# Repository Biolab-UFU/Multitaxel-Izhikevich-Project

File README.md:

# Sensor Multitaxel com Modelo de Izhikevich

## 📌 **Descrição do Projeto**
Este projeto consiste na aplicação do **Modelo de Izhikevich** para a detecção de **escorregamento** em uma **matriz piezoresistiva**, acoplada à ponta dos dedos de uma **prótese robótica**. A matriz é composta por **4 linhas e 4 colunas**, formando um total de **16 unidades tácteis (taxels)**.

A leitura do sensor é realizada por uma **placa Nucleo STM32F767ZI**, com o firmware desenvolvido na **STM32CubeIDE**. O processamento do sinal permite detectar padrões tácteis e inferir a presença de escorregamento, contribuindo para o aprimoramento do controle da prótese.

---

## 🛠 **Arquitetura do Sistema**
### 🔹 **Hardware**
- **Matriz piezoresistiva:** 4×4 taxels.
- **Placa de aquisição:** Utiliza **multiplexadores** para selecionar os taxels.
- **Filtro passa-baixa de 10Hz:** Realiza o pré-processamento dos sinais.
- **STM32F767ZI:** Responsável pela aquisição e processamento do sinal.

### 🔹 **Esquema de Leitura**
- **As 4 colunas** da matriz estão conectadas aos **canais do ADC1** do STM32F767, com **pull-up de 5.6kΩ**.
- **As 4 linhas** estão conectadas a **GPIOs** e são ativadas sequencialmente para permitir a multiplexação.
- O firmware controla a ativação das linhas e a aquisição dos valores analógicos das colunas via **ADC**, permitindo a reconstrução da distribuição de pressão na matriz.

---

## 🧠 **Modelo de Izhikevich**
O modelo de **Izhikevich (2003)** é um modelo matemático de neurônios que equilibra **simplicidade computacional** e **realismo biológico**. Ele é definido pelas seguintes equações diferenciais:

$$
\frac{dv}{dt} = 0.04v^2 + 5v + 140 - u + I
$$

$$
\frac{du}{dt} = a(bv - u)
$$

Se v ≥ 30mV, então: v ← c, u ← u + d

Onde:
- **v** representa o potencial de membrana do neurônio.
- **u** é uma variável de recuperação do neurônio.
- **I** é a corrente de entrada.
- **a, b, c, d** são parâmetros ajustáveis que definem diferentes tipos de comportamento neural.

Quando **v atinge 30mV**, ocorre um disparo neuronal, e ele é resetado.

No contexto deste projeto, esse modelo é aplicado à saída da matriz tátil, permitindo a identificação de padrões temporais associados ao **escorregamento**.

---

## 📂 **Estrutura do Repositório**
📁 /STM32F767 - A documentação necessária para o desenvolvimento na Nucleo Board (Ler Main User Manual e Reference Manual).  

📁 /hardware - Hardware, Esquemáticos e diagramas do sensor multitaxel.  

📁 /firmware - Código-fonte para aquisição, geração e processamento dos sinais, e visualização gráfica.  

📁 /Artigos - Artigos desenvolvidos pelo Biolab, e pelo laboratório SINAPSE de Singapura (fabricante do sensor), além de artigos úteis.  

Cada subdiretório contém um **README** específico com detalhes sobre sua funcionalidade.

---

## 🚀 **Como Usar**
### 📌 **Requisitos**
- **Placa STM32F767ZI**
- **STM32CubeIDE**
- **Cabo USB para programação**

### 🔧 **Passos**
1. Clone este repositório:  
   ```bash
   git clone https://github.com/stephan-biomedical-engineer/Biolab.git
   ```
2. Abra o **STM32CubeIDE** e importe o projeto.
3. Compile e grave o firmware na placa.
4. Conecte o sensor e monitore a aquisição dos sinais.

---

## 📜 **Referências**
- Izhikevich, E. M. (2003). "Simple Model of Spiking Neurons". _IEEE Transactions on Neural Networks._
- Documentação da **STMicroelectronics** para o STM32F767ZI.

---

📌 **Autor:** Stephan Costa Barros  
📅 **Última atualização:** 29/03/2025
💡 **Contato:** stephanbrrs8@gmail.com

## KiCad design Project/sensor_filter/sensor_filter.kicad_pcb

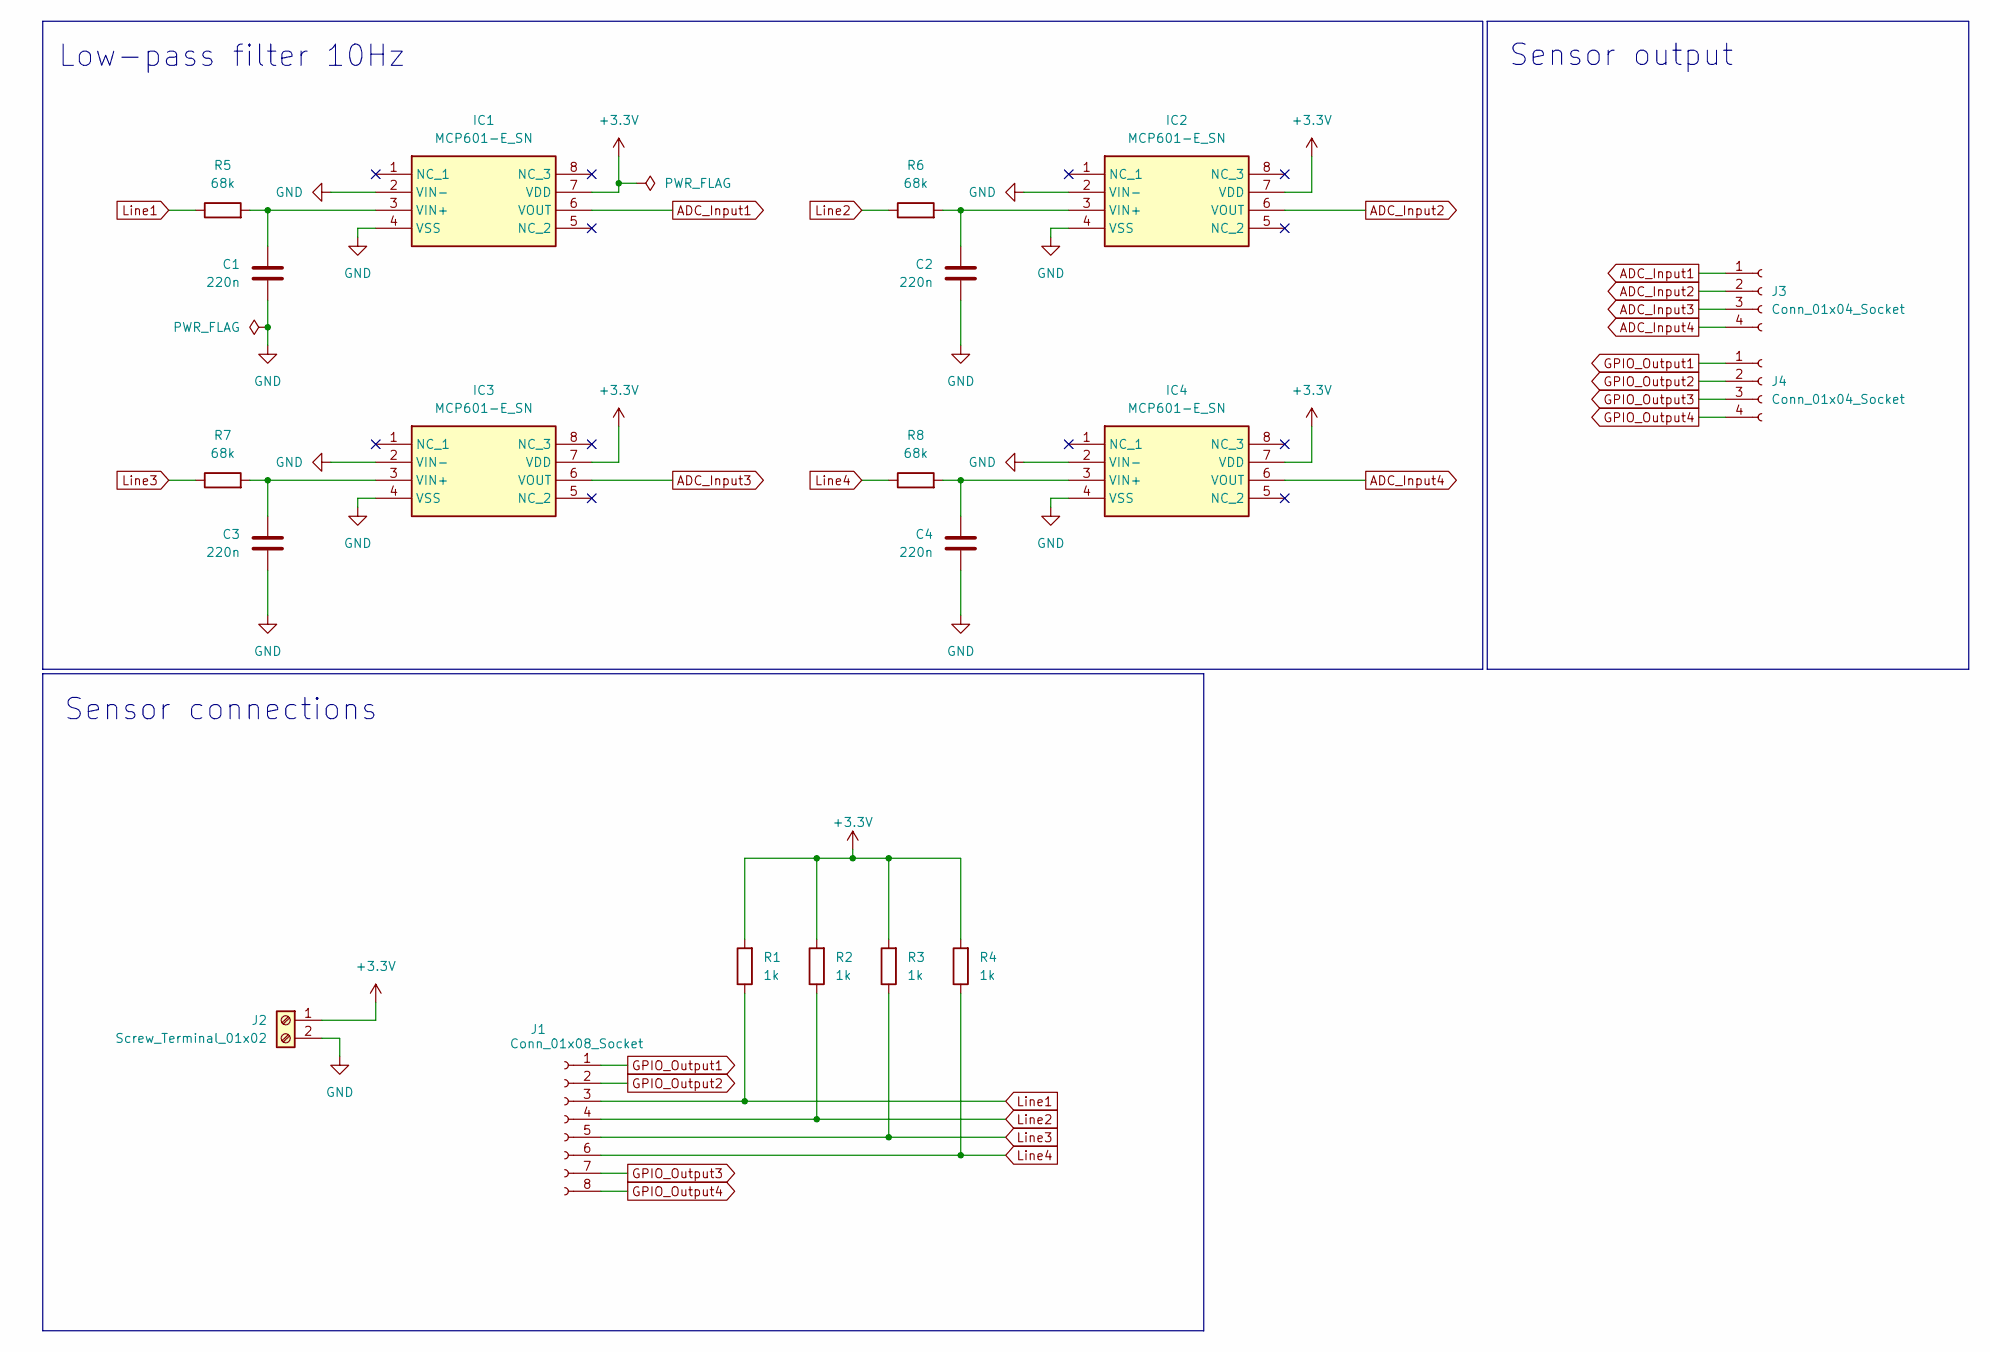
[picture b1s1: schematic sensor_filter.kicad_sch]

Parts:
C1, C2, C3, C4: 220n; CP_Radial_Tantal_D4.5mm_P2.50mm
IC1, IC2, IC3, IC4: MCP601-E_SN; SOIC127P600X175-8N; Mouser Part Number 579-MCP601-E/SN
J1: Conn_01x08_Socket; PinSocket_1x08_P2.54mm_Vertical
J2: Screw_Terminal_01x02; TerminalBlock_MaiXu_MX126-5.0-02P_1x02_P5.00mm
J3, J4: Conn_01x04_Socket; PinSocket_1x04_P2.54mm_Vertical
R1, R2, R3, R4: 1k; R_Axial_DIN0207_L6.3mm_D2.5mm_P7.62mm_Horizontal
R5, R6, R7, R8: 68k; R_Axial_DIN0207_L6.3mm_D2.5mm_P7.62mm_Horizontal

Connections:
+3.3V: IC1.7 (VDD), IC2.7 (VDD), IC3.7 (VDD), IC4.7 (VDD), J2.1, R1.2, R2.2, R3.2, R4.2
ADC_Input1: IC1.6 (VOUT), J3.1
ADC_Input2: IC2.6 (VOUT), J3.2
ADC_Input3: IC3.6 (VOUT), J3.3
ADC_Input4: IC4.6 (VOUT), J3.4
GND: C1.2, C2.2, C3.2, C4.2, IC1.2 (VIN-), IC1.4 (VSS), IC2.2 (VIN-), IC2.4 (VSS), IC3.2 (VIN-), IC3.4 (VSS), IC4.2 (VIN-), IC4.4 (VSS), J2.2
GPIO_Output1: J1.1, J4.1
GPIO_Output2: J1.2, J4.2
GPIO_Output3: J1.7, J4.3
GPIO_Output4: J1.8, J4.4
Line1: J1.3, R1.1, R5.1
Line2: J1.4, R2.1, R6.1
Line3: J1.5, R3.1, R7.1
Line4: J1.6, R4.1, R8.1
unnamed: C1.1, IC1.3 (VIN+), R5.2
unnamed: C2.1, IC2.3 (VIN+), R6.2
unnamed: C3.1, IC3.3 (VIN+), R7.2
unnamed: C4.1, IC4.3 (VIN+), R8.2

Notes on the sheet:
Sensor connections
Low-pass filter 10Hz
Sensor output

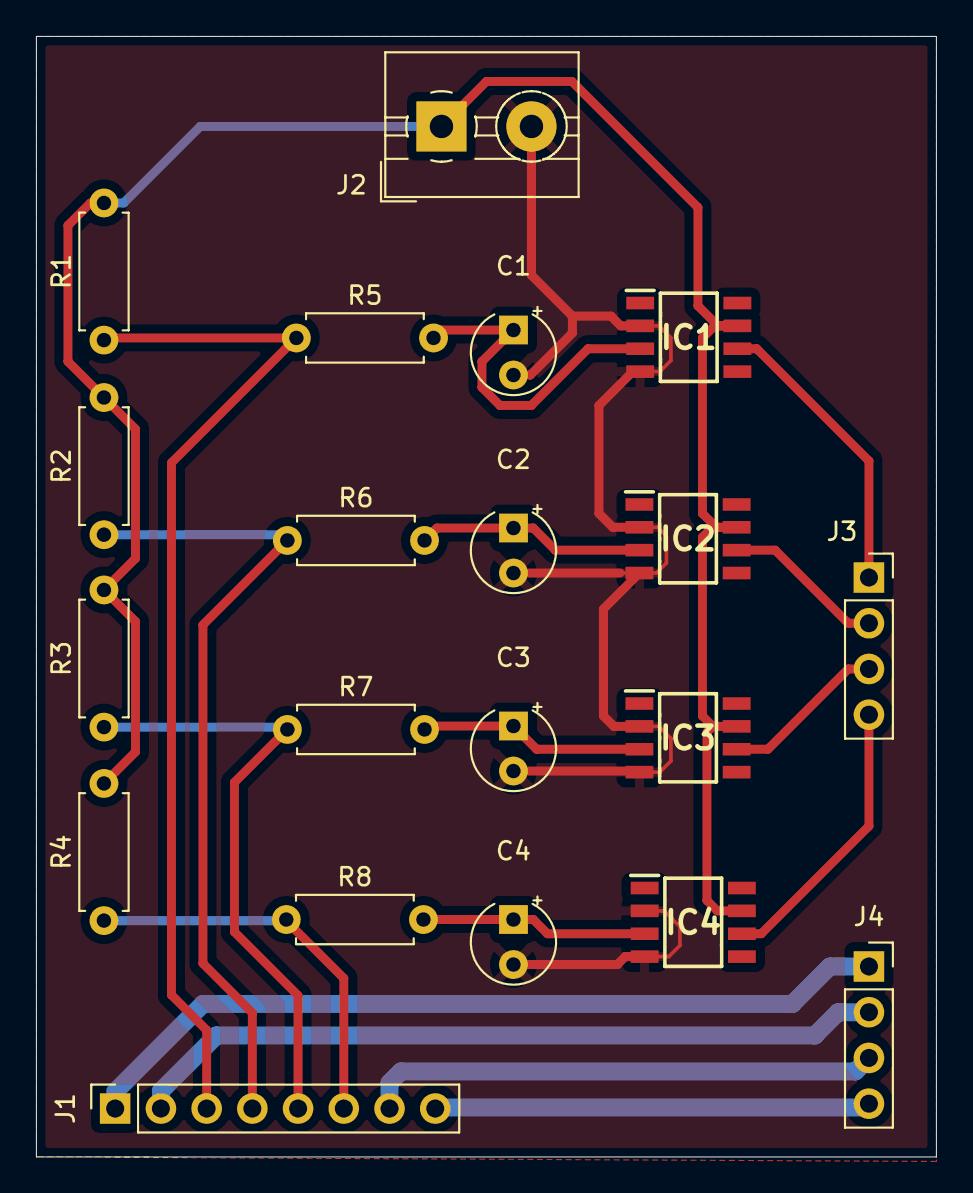
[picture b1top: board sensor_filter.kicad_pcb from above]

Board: 2 copper layers, 50.0 x 62.2 mm, 20 parts (0 on the bottom side), 18 nets.

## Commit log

2025-01-13 STM32CubeIDE Project
2025-01-24 stm32 code
2025-01-31 Izhikevich for Arduino
2025-02-05 Correção TIM6
2025-02-06 Tirei a normalização do sinal
2025-02-25 Inclusao da placa de aquisicao
2025-03-29 Inclusão de projetos antigos e finalizando Firmware
2025-03-29 Removendo sub-diretorios
2025-03-30 Versão Final
2025-03-30 Remoção de sub-diretórios
2025-03-30 Low-pass-filter board KiCAD
2025-03-30 Artigos para entender o projeto
2025-03-30 README
2025-03-30 Adicionando Hardware e Firmware como sub-diretorios
2025-03-30 Adicionando Hardware e Firmware como sub-diretórios
2025-03-30 Att do hardware
2025-03-30 README.md
2025-03-30 Imagens do projeto
2025-03-31 Inclusão de Artigo do CBEB
2025-03-31 Recomendações de uso do STM32F767
2025-03-31 README.md para uso do STM32F767
2025-03-31 Videos de funcionamento
2025-04-01 Adição dos vídeos
2025-04-01 Diretório do Manipulador Robótico para sistema de controle realimentado
2025-05-16 Inclusões de artigo e metadata do firmware
2025-08-15 .metadata exclusion
2025-08-15 exclusion of metadata files from firmware
2025-08-15 Remove IDE-generated files (.metadata, Debug, Release) and add to .gitignore
2025-08-15 Circular Buffer Inclusion
2025-08-15 UART pins ioc selected
